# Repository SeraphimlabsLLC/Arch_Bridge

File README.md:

# Arch_Bridge

DCC-EX to Loconet accessory bus interface with throttle and booster driving. 

Additional 2A booster channel for future use

 Bidirectional transmission of turnout commands from Loconet to DCC-EX
 One way Throttle transmission, Loconet to DCC-EX

 Fastclock supplied to DCC-EX, still WIP getting it on Loconet

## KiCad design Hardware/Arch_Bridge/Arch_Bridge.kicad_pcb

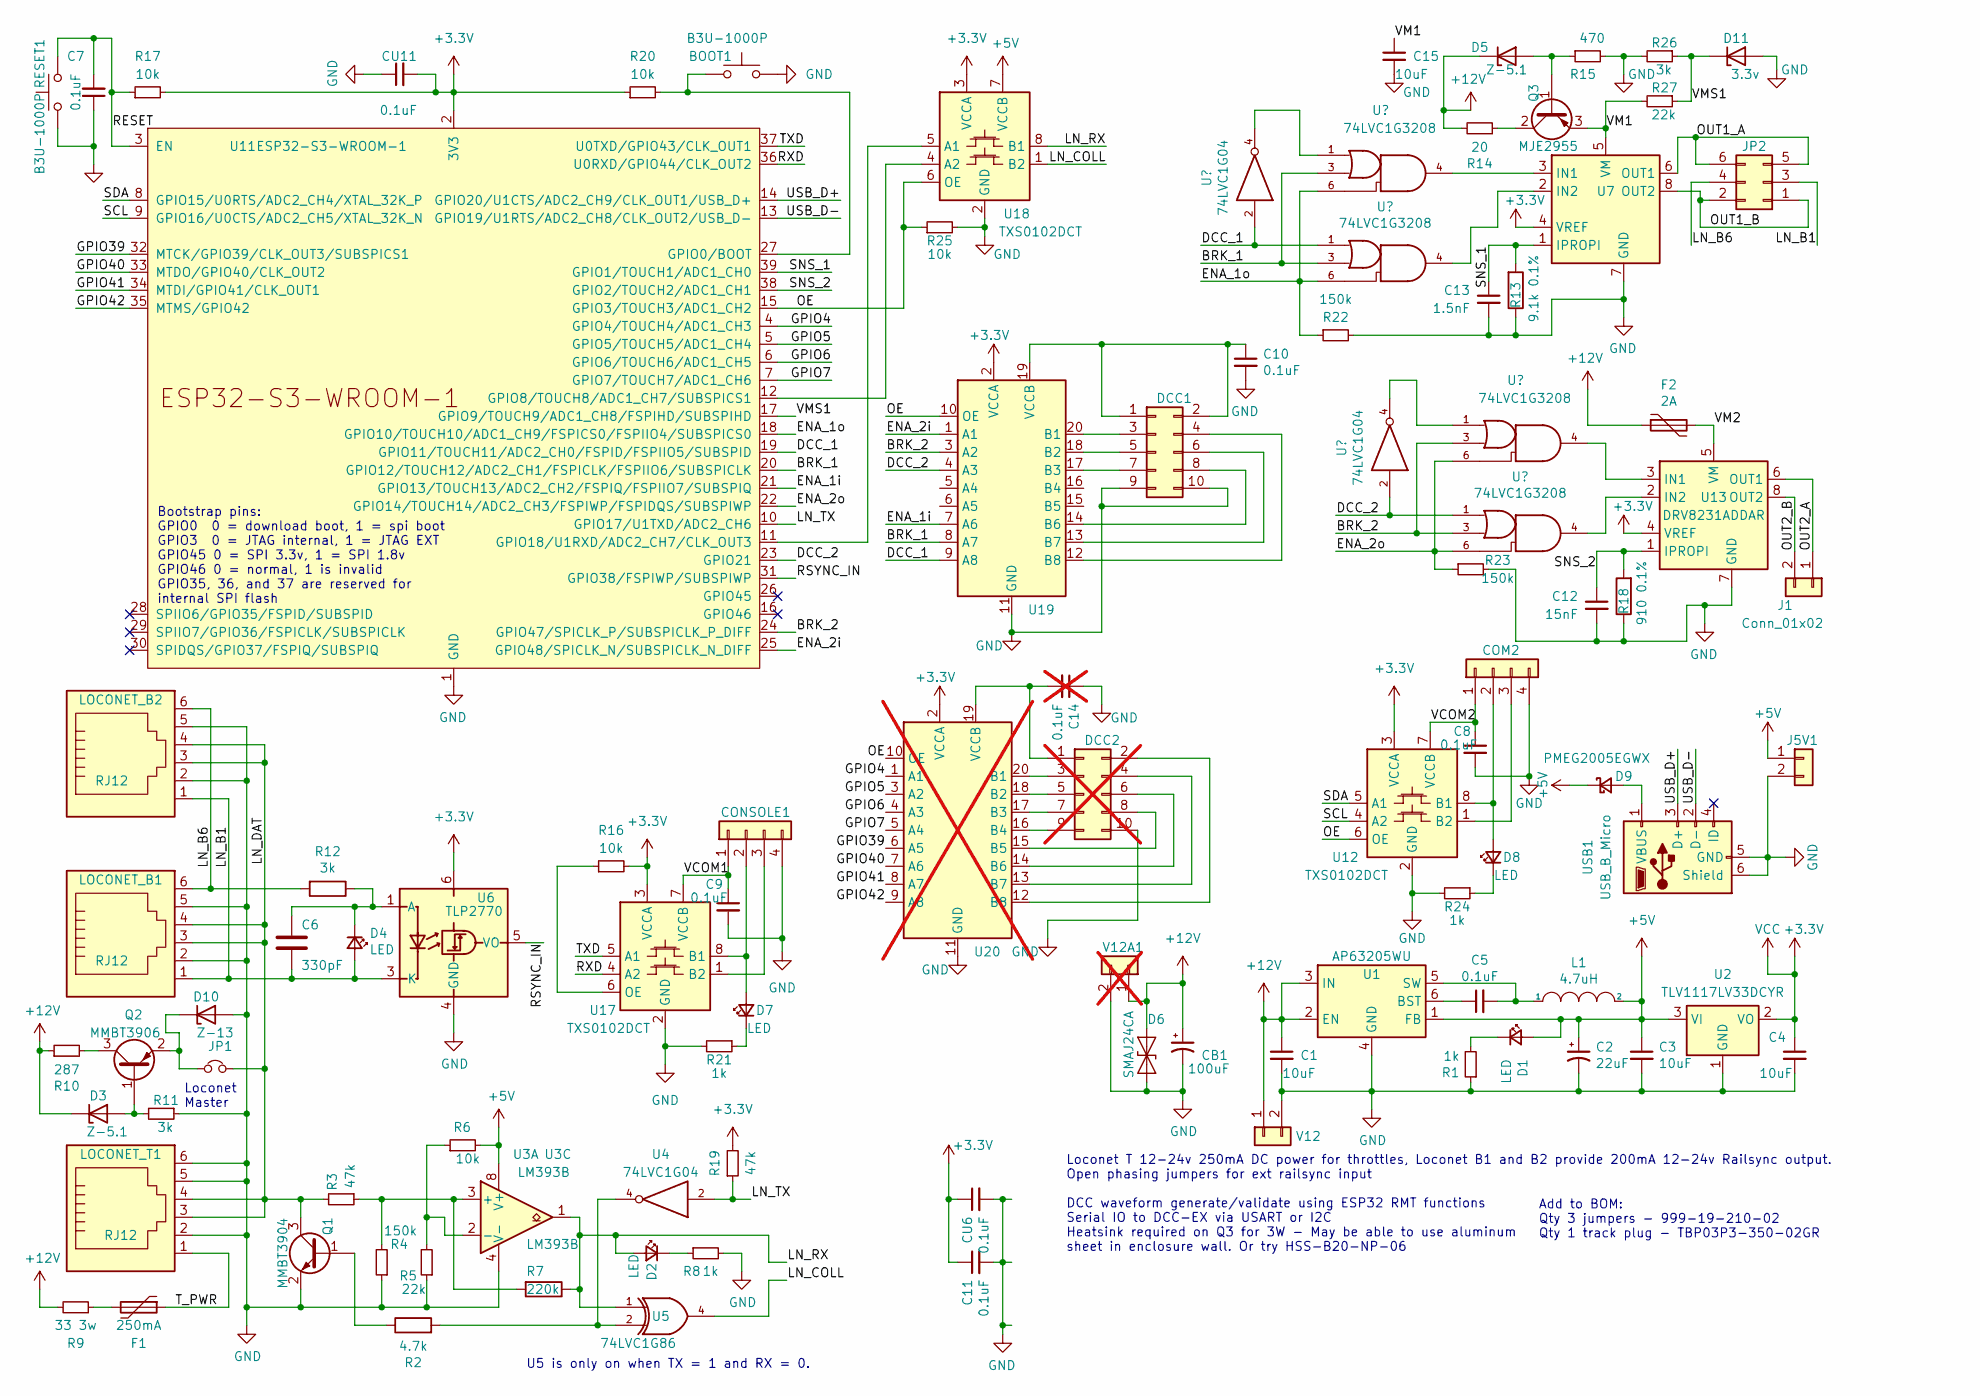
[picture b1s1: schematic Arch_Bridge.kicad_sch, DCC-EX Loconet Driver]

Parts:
BOOT1: B3U-1000P; SW_SPST_B3U-1000P-B; LCSC SKU C231329
C1, C3, C4, C15: 10uF; C_1210_3225Metric; LCSC SKU C380537
C2: 22uF; CP_Elec_5x5.3; LCSC SKU C2164091
C5, C7, C8, C9, C10, C11: 0.1uF; C_1206_3216Metric; LCSC SKU C600013
C6: 330pF; C_1206_3216Metric; LCSC SKU C2223641
C12: 15nF; C_1206_3216Metric_Pad1.33x1.80mm_HandSolder; LCSC SKU C2174116
C13: 1.5nF; C_1206_3216Metric_Pad1.33x1.80mm_HandSolder; LCSC SKU C2230319
C14: 0.1uF; C_1206_3216Metric; LCSC SKU C600013; not fitted
CB1: 100uF; CP_Elec_8x10; LCSC SKU C696384
COM2: Conn_01x04; PinSocket_1x04_P2.54mm_Vertical; LCSC SKU C3323964
CONSOLE1: Conn_01x04; PinSocket_1x04_P2.54mm_Vertical; LCSC SKU C3323964
CU6, CU11: 0.1uF; C_1206_3216Metric; LCSC SKU C600013
D1, D2, D4, D7, D8: LED; LED_1206_3216Metric
D3, D5: Z-5.1; D_MiniMELF; LCSC SKU C550442
D6: SMAJ24CA; D_SMA; LCSC SKU C148223
D9: PMEG2005EGWX; D_SOD-123; LCSC SKU C552812
D10: Z-13; D_MiniMELF; LCSC SKU C550391
D11: 3.3v; D_MiniMELF; LCSC SKU C550442
DCC1: Conn_02x05_Odd_Even; PinSocket_2x05_P2.54mm_Vertical; LCSC SKU C6235491
DCC2: Conn_02x05_Odd_Even; PinSocket_2x05_P2.54mm_Vertical; LCSC SKU C6235491; not fitted
F1: 250mA; Fuse_1206_3216Metric; LCSC SKU C2442492
F2: 2A; Fuse_Bourns_MF-RHT200; LCSC SKU C2153889
J1: Conn_01x02; PhoenixContact_MC_1,5_2-G-3.5_1x02_P3.50mm_Horizontal; LCSC SKU C880572
J5V1: Conn_01x02; PinSocket_1x02_P2.54mm_Vertical; LCSC SKU C3323491
JP1: Jumper_NC_Small; PinHeader_1x02_P2.54mm_Vertical; LCSC SKU C5172712
JP2: Conn_02x03_Odd_Even; PinHeader_2x03_P2.54mm_Vertical; LCSC SKU C6360273
L1: 4.7uH; L_Wurth_WE-LQSH-4020; LCSC SKU C167828
LOCONET_B1, LOCONET_B2: RJ12; RJ12_Amphenol_54601; LCSC SKU C4355015
LOCONET_T1: RJ12; RJ12_Amphenol_54601; LCSC SKU C4355015
Q1: MMBT3904; SOT-23; LCSC SKU C77991
Q2: MMBT3906; SOT-23; LCSC SKU C77990
Q3: MJE2955; TO-220-3_Vertical; LCSC SKU C184196
R1, R8, R21, R24: 1k; R_1206_3216Metric; LCSC SKU C131398
R2: 4.7k; R_1206_3216Metric; LCSC SKU C3975500
R3, R19: 47k; R_1206_3216Metric; LCSC SKU C137270
R4, R22, R23: 150k; R_1206_3216Metric; LCSC SKU C114931
R5, R27: 22k; R_1206_3216Metric; LCSC SKU C114942
R6, R16, R17, R20, R25: 10k; R_1206_3216Metric; LCSC SKU C4303232
R7: 220k; R_1206_3216Metric; LCSC SKU C130275
R9: 33 3w; R_Axial_DIN0516_L15.5mm_D5.0mm_P5.08mm_Vertical; LCSC SKU C1761032
R10: 287; R_1206_3216Metric; LCSC SKU C488764
R11, R12, R26: 3k; R_1206_3216Metric; LCSC SKU C132648
R13: 9.1k 0.1%; R_1206_3216Metric; LCSC SKU C706423
R14: 20; R_2512_6332Metric; LCSC SKU C309605
R15: 470; R_2512_6332Metric; LCSC SKU C872782
R18: 910 0.1%; R_1206_3216Metric; LCSC SKU C870936
RESET1: B3U-1000P; SW_SPST_B3U-1000P-B; LCSC SKU C231329
U1: AP63205WU; TSOT-23-6; LCSC SKU C2071056
U2: TLV1117LV33DCYR; SOT-223-3_TabPin2; LCSC SKU C91728
U3: LM393B; SOIC-8_3.9x4.9mm_P1.27mm; LCSC SKU C2865059
U4, U10, U16: 74LVC1G04; SOT-23-5_HandSoldering; LCSC SKU C7827
U5: 74LVC1G86; SOT-23-5_HandSoldering; LCSC SKU C402161
U6: TLP2770; SO-6L_10x3.84mm_P1.27mm; LCSC SKU C150160
U7, U13: DRV8231ADDAR; Texas_HTSOP-8-1EP_3.9x4.9mm_P1.27mm_EP2.95x4.9mm_Mask2.4x3.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
U8, U9, U14, U15: 74LVC1G3208; SOT-23-6_Handsoldering; LCSC SKU C2682152
U11: ESP32-S3-WROOM-1; ESP32-S3-WROOM-1U; LCSC SKU C2980298
U12, U17, U18: TXS0102DCT; SSOP-8_2.95x2.8mm_P0.65mm; LCSC SKU C2677354
U19: TXB0108PWR; TSSOP-20_4.4x6.5mm_P0.65mm; LCSC SKU C53406
U20: TXB0108PWR; TSSOP-20_4.4x6.5mm_P0.65mm; LCSC SKU C53406; not fitted
USB1: USB_B_Micro; USB_Micro-B_Molex-105017-0001; LCSC SKU C136000
V12: Conn_01x02; PhoenixContact_MSTBA_2,5_2-G_1x02_P5.00mm_Horizontal
V12A1: Conn_01x02; Screw_Terminal_2pin_Multicomp; not fitted

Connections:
+3.3V: C4.1, C11.1, CU6.1, CU11.2, R16.2, R17.2, R19.2, R20.1, U2.2 (VO), U6.6, U7.4 (VREF), U8.5 (VCC), U9.5 (VCC), U10.5 (VCC), U11.2 (3V3), U12.3 (VCCA), U13.4 (VREF), U14.5 (VCC), U15.5 (VCC), U16.5 (VCC), U17.3 (VCCA), U18.3 (VCCA), U19.2 (VCCA), U20.2 (VCCA)
+5V: C2.1, C3.1, D1.2 (A), D9.1 (K), J5V1.1, L1.2, R6.2, U1.1 (FB), U2.3 (VI), U3.8 (V+), U4.5 (+5V), U5.5 (+5V), U18.7 (VCCB)
+12V: C1.1, CB1.1, D3.1 (K), D5.1 (K), D6.1 (A1), F2.1, R9.2, R10.1, R14.2, U1.2 (EN), U1.3 (IN), V12.1, V12A1.1
/BRK_1: U8.3, U9.3, U11.20 (GPIO12/TOUCH12/ADC2_CH1/FSPICLK/FSPIIO6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), U19.8 (A7)
/BRK_2: U11.24 (GPIO47/SPICLK_P/SUBSPICLK_P_DIFF), U14.3, U15.3, U19.3 (A2)
/DCC_1: U9.1, U10.2, U11.19 (GPIO11/TOUCH11/ADC2_CH0/FSPID/FSPIIO5/S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), U19.9 (A8)
/DCC_2: U11.23 (GPIO21), U15.1, U16.2, U19.4 (A3)
/ENA_1i: U11.21 (GPIO13/TOUCH13/ADC2_CH2/FSPIQ/FSPIIO7/S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), U19.7 (A6)
/ENA_1o: R22.1, U8.6, U9.6, U11.18 (GPIO10/TOUCH10/ADC1_CH9/FSPICS0/FSPIIO4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)
/ENA_2i: U11.25 (GPIO48/SPICLK_N/SUBSPICLK_N_DIFF), U19.1 (A1)
/ENA_2o: R23.1, U11.22 (GPIO14/TOUCH14/ADC2_CH3/FSPIWP/FSPIDQS/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), U14.6, U15.6
/GPIO4: U11.4 (GPIO4/TOUCH4/ADC1_CH3), U20.1 (A1)
/GPIO5: U11.5 (GPIO5/TOUCH5/ADC1_CH4), U20.3 (A2)
/GPIO6: U11.6 (GPIO6/TOUCH6/ADC1_CH5), U20.4 (A3)
/GPIO7: U11.7 (GPIO7/TOUCH7/ADC1_CH6), U20.5 (A4)
/GPIO39: U11.32 (MTCK/GPIO39/CLK_OUT3/SUBSPICS1), U20.6 (A5)
/GPIO40: U11.33 (MTDO/GPIO40/CLK_OUT2), U20.7 (A6)
/GPIO41: U11.34 (MTDI/GPIO41/CLK_OUT1), U20.8 (A7)
/GPIO42: U11.35 (MTMS/GPIO42), U20.9 (A8)
/LN_B1: C6.2, D4.2 (A), JP2.3, LOCONET_B1.1, LOCONET_B2.1, U6.3 (K)
/LN_B6: JP2.4, LOCONET_B1.6, LOCONET_B2.6, R12.2
/LN_COLL: U5.4, U18.1 (B2)
/LN_DAT: JP1.2, LOCONET_B1.3, LOCONET_B1.4, LOCONET_B2.3, LOCONET_B2.4, LOCONET_T1.3, LOCONET_T1.4, Q1.3 (C), R3.2
/LN_RX: D2.2 (A), R7.1, U3.1, U5.1, U18.8 (B1)
/LN_TX: R19.1, U4.2, U11.10 (GPIO17/U1TXD/ADC2_CH6)
/OE: R25.1, U11.15 (GPIO3/TOUCH3/ADC1_CH2), U12.6 (OE), U18.6 (OE), U19.10 (OE), U20.10 (OE)
/OUT1_A: JP2.5, JP2.6, U7.6 (OUT1)
/OUT1_B: JP2.1, JP2.2, U7.8 (OUT2)
/OUT2_A: J1.1, U13.6 (OUT1)
/OUT2_B: J1.2, U13.8 (OUT2)
/RESET: C7.2, R17.1, RESET1.2, U11.3 (EN)
/RSYNC_IN: U6.5 (VO), U11.31 (GPIO38/FSPIWP/SUBSPIWP)
/RXD: U11.36 (U0RXD/GPIO44/CLK_OUT2), U17.4 (A2)
/SCL: U11.9 (GPIO16/U0CTS/ADC2_CH5/XTAL_32K_N), U12.4 (A2)
/SDA: U11.8 (GPIO15/U0RTS/ADC2_CH4/XTAL_32K_P), U12.5 (A1)
/SNS_1: C13.1, R13.2, U7.1 (IPROPI), U11.39 (GPIO1/TOUCH1/ADC1_CH0)
/SNS_2: C12.1, R18.2, U11.38 (GPIO2/TOUCH2/ADC1_CH1), U13.1 (IPROPI)
/TXD: U11.37 (U0TXD/GPIO43/CLK_OUT1), U17.5 (A1)
/T_PWR: F1.1, LOCONET_T1.1
/USB_D+: U11.14 (GPIO20/U1CTS/ADC2_CH9/CLK_OUT1/USB_D+), USB1.3 (D+)
/USB_D-: U11.13 (GPIO19/U1RTS/ADC2_CH8/CLK_OUT2/USB_D-), USB1.2 (D-)
/VCOM1: C9.1, CONSOLE1.1, U17.7 (VCCB)
/VCOM2: C8.1, COM2.1, U12.7 (VCCB)
/VM1: C15.1, Q3.3 (E), R27.2, U7.5 (VM)
/VM2: F2.2, U13.5 (VM)
/VMS1: D11.1 (K), R26.1, R27.1, U11.17 (GPIO9/TOUCH9/ADC1_CH8/FSPIHD/SUBSPIHD)
GND: BOOT1.1, C1.2, C2.2, C3.2, C4.2, C7.1, C8.2, C9.2, C10.2, C11.2, C12.2, C13.2, C14.1, C15.2, CB1.2, COM2.4, CONSOLE1.4, CU6.2, CU11.1, D6.2 (A2), D10.2 (A), D11.2 (A), DCC1.9, DCC1.10, DCC2.10, J5V1.2, LOCONET_B1.2, LOCONET_B1.5, LOCONET_B2.2, LOCONET_B2.5, LOCONET_T1.2, LOCONET_T1.5, LOCONET_T1.6, Q1.2 (E), R1.1, R4.1, R5.1, R8.2, R11.1, R13.1, R15.2, R18.1, R21.2, R22.2, R23.2, R24.2, R25.2, R26.2, RESET1.1, U1.4 (GND), U2.1 (GND), U3.4 (V-), U4.3 (GND), U5.3 (GND), U6.4 (GND), U7.7 (GND), U7.9 (GND), U8.2 (GND), U9.2 (GND), U10.3 (GND), U11.1 (GND), U11.40 (GND), U11.41 (GND), U12.2 (GND), U13.7 (GND), U13.9 (GND), U14.2 (GND), U15.2 (GND), U16.3 (GND), U17.2 (GND), U18.2 (GND), U19.11 (GND), U20.11 (GND), USB1.5 (GND), USB1.6 (Shield), V12.2, V12A1.2; also elsewhere on the board
unnamed: COM2.2, D8.2 (A), U12.8 (B1)
unnamed: COM2.3, U12.1 (B2)
unnamed: CONSOLE1.2, D7.2 (A), U17.8 (B1)
unnamed: CONSOLE1.3, U17.1 (B2)
unnamed: D1.1 (K), R1.2
unnamed: D2.1 (K), R8.1
unnamed: D3.2 (A), Q2.1 (B), R11.2
unnamed: C6.1, D4.1 (K), R12.1, U6.1 (A)
unnamed: D5.2 (A), Q3.1 (B), R15.1
unnamed: D7.1 (K), R21.1
unnamed: D8.1 (K), R24.1
unnamed: D9.2 (A), USB1.1 (VBUS)
unnamed: D10.1 (K), JP1.1, Q2.2 (E)
unnamed: C10.1, DCC1.1, DCC1.2, U19.19 (VCCB)
unnamed: DCC1.3, U19.20 (B1)
unnamed: DCC1.4, U19.12 (B8)
unnamed: DCC1.5, U19.18 (B2)
unnamed: DCC1.6, U19.13 (B7)
unnamed: DCC1.7, U19.17 (B3)
unnamed: DCC1.8, U19.14 (B6)
unnamed: C14.2, DCC2.1, U20.19 (VCCB)
unnamed: DCC2.2, U20.12 (B8)
unnamed: DCC2.3, U20.20 (B1)
unnamed: DCC2.4, U20.13 (B7)
unnamed: DCC2.5, U20.18 (B2)
unnamed: DCC2.6, U20.14 (B6)
unnamed: DCC2.7, U20.17 (B3)
unnamed: DCC2.8, U20.15 (B5)
unnamed: DCC2.9, U20.16 (B4)
unnamed: F1.2, R9.1
unnamed: Q1.1 (B), R2.1
unnamed: Q2.3 (C), R10.2
unnamed: Q3.2 (C), R14.1
unnamed: R2.2, U4.4, U5.2
unnamed: C5.1, U1.6 (BST)
unnamed: C5.2, L1.1, U1.5 (SW)
unnamed: R3.1, R4.2, R7.2, U3.3 (+)
unnamed: R5.2, R6.1, U3.2 (-)
unnamed: U7.3 (IN1), U8.4
unnamed: U7.2 (IN2), U9.4
unnamed: U8.1, U10.4
unnamed: BOOT1.2, R20.2, U11.27 (GPIO0/BOOT)
unnamed: U11.12 (GPIO8/TOUCH8/ADC1_CH7/SUBSPICS1), U18.4 (A2)
unnamed: U11.11 (GPIO18/U1RXD/ADC2_CH7/CLK_OUT3), U18.5 (A1)
unnamed: U13.3 (IN1), U14.4
unnamed: U13.2 (IN2), U15.4
unnamed: U14.1, U16.4
unnamed: R16.1, U17.6 (OE)

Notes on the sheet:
Loconet T 12-24v 250mA DC power for throttles, Loconet B1 and B2 provide 200mA 12-24v Railsync output. Open phasing jumpers for ext railsync input DCC waveform generate/validate using ESP32 RMT functions Serial IO to DCC-EX via USART or I2C Heatsink required on Q3 for 3W - May be able to use alumin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
U5 is only on when TX = 1 and RX = 0.
Loconet Master
Add to BOM: Qty 3 jumpers - 999-19-210-02 Qty 1 track plug - TBP03P3-350-02GR
Bootstrap pins: GPIO0 0 = download boot, 1 = spi boot GPIO3 0 = JTAG internal, 1 = JTAG EXT GPIO45 0 = SPI 3.3v, 1 = SPI 1.8v GPIO46 0 = normal, 1 is invalid GPIO35, 36, and 37 are reserved for internal SPI flash

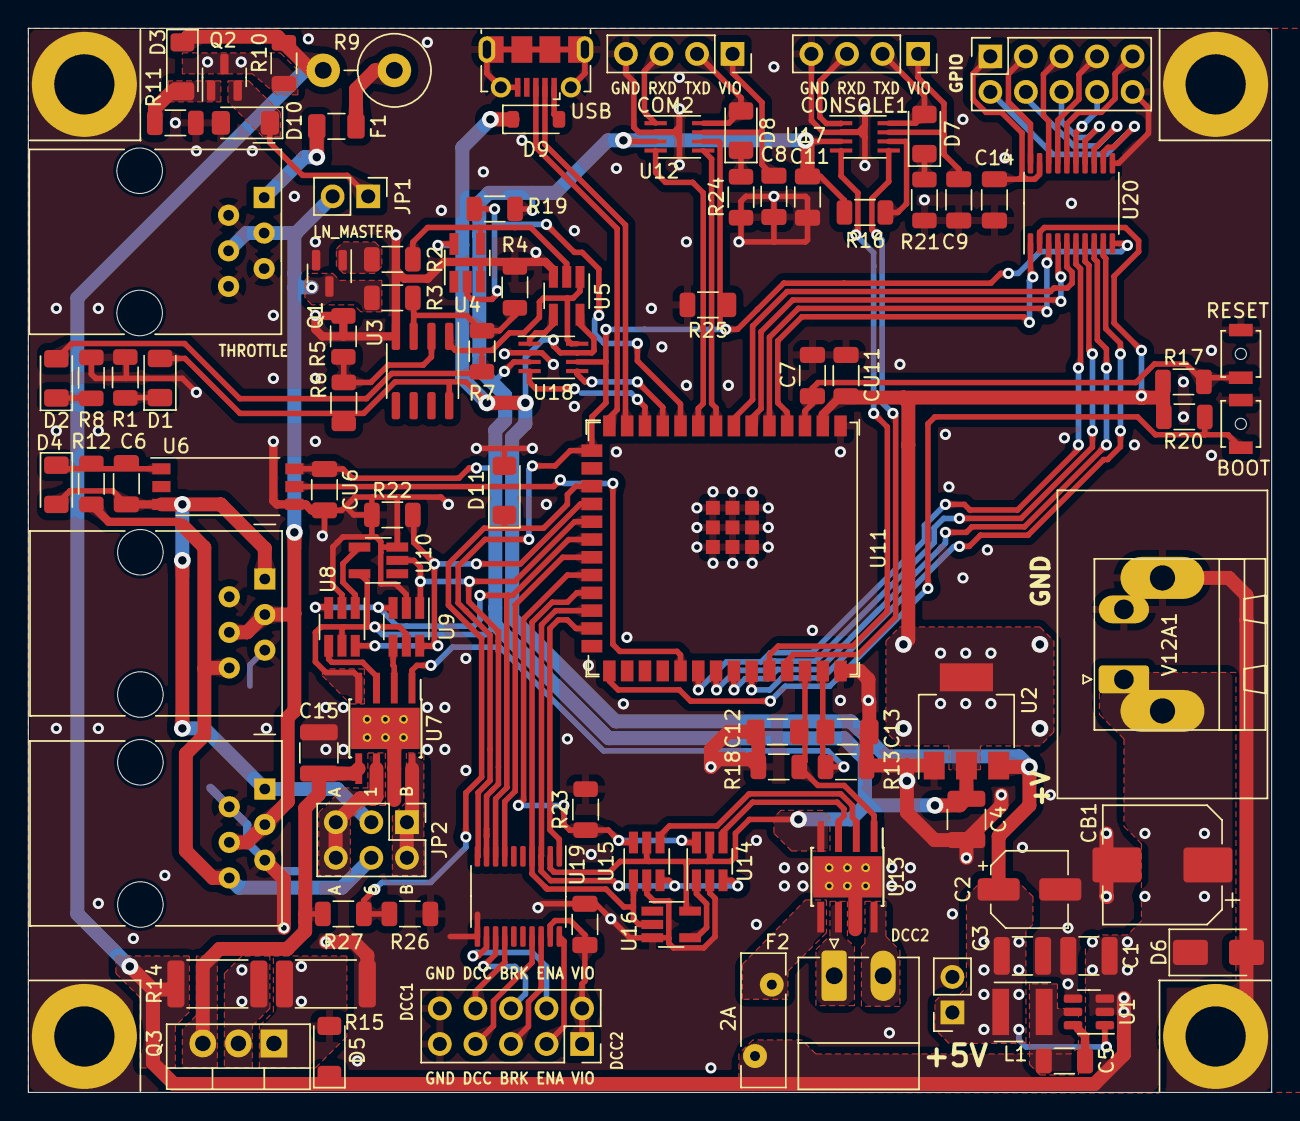
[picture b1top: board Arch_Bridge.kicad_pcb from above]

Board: 2 copper layers, 88.8 x 76.0 mm, 101 parts (0 on the bottom side), 95 nets.

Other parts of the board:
H1, H2, H4: MountingHole_Pad; MountingHole_4.3mm_M4_DIN965_Pad

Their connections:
GND: H1.1, H2.1, H4.1; also elsewhere on the board

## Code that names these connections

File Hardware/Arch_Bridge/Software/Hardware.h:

//ADC Settings:
#DEFINE ADC_DMAX 4095 //4095 in single shot, 8191 in continuous
#DEFINE ADC_VMAX 3.1 //Max readable voltage is actually 3.1v using mode ADC_ATTEN_DB_11  

//TTY settings:
/* Pin Map
TXD = GPIO43(U0TXD)
RXD = GPIO44(U0RXD)
*/
#DEFINE TTY_TX_BUFF = 4096
#DEFINE TTY_RX_BUFF = 4096

//I2C settings: 
/* Pin Map
SDA = GPIO15
SCL = GPIO16
*/
#DEFINE I2C_TX_BUFF = 4096
#DEFINE I2C_RX_BUFF = 4096

//Loconet settings:
/* Pin Map
LN_TX = GPIO17(U1RXD)
LN_RX = GPIO18 (U1RXD)
LN_COLL = GPIO0
*/
#DEFINE LN_TX_BUFF = 4096
#DEFINE LN_RX_BUFF = 4096

//Railsync input settings:
/* Pin Map
RSYNC_IN = GPIO9
*/

//Railsync output settings:
/*  Pin Map
ENA_10 = GPIO10
DCC_1 = GPIO11
BRK_1 = GPIO12
ENA_1i = GPIO13
SNS1 = GPIO1(ADC1_CH0)
*/
#DEFINE OUT1_MAX_A 3610 //ADC_DMAX / ADC_VMAX * SENSE_V for 200mA + 0.1%

//Track output settings:
/* Pin Map
ENA_20 = GPIO14
DCC_2 = GPIO21
BRK_2 = GPIO47
ENA_2i = GPIO48
SNS2 = GPIO2(ADC1_CH1)
*/
#DEFINE OUT2_MAX_A 3610 //ADC_DMAX / ADC_VMAX * SENSE_V for 2A + 0.1%

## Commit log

2023-07-27 Adding hardware brief in README.md
2023-07-27 Folder structure for hardware/software and KiCad solution
2023-07-30 Completed BOM, PCB layout cleanup, starting software.
2023-07-30 Add PDF schematic
2023-07-30 Configured initial .gitignore
2023-08-20 Revised L1 for possible 2A output, cleaner fill zones, fabrication outputs
2023-08-21 BOM Cleanup, substitute 3.3v LDO for easier to get part.
2023-08-27 Update .gitignore
    Ignore KiCad backups
2023-09-28 First build using this hardware for software development.
2023-09-28 Added .gitignore
2023-09-29 ESP_Uart class added, has problems still and Arduino Serial library acting as a placeholder.
2023-09-29 Prep to move uart code and loconet code into separate files
2023-09-29 Rough split of uart code into its own files
2023-10-03 Power modes partially implemented. Railsync output H bridge handled a test waveform correctly.
2023-10-09 ADC testing, progress reading from Loconet.
2023-10-12 Progress on Loconet parser
2023-10-16 Loconet RX/TX still not working.
2023-10-16 Loconet uart is able to send data, but still needs transmission rules
2023-10-16 Loconet UART working in both RX and TX. Can finally write the parsers.
2023-10-21 Progress on DCC-EX parser
2023-10-21 Fixed R11 value, 33k => 3k so that Q2 sources correctly. Tested at 14.5mA on a 12v supply.
2023-10-22 Adjusted R15 value and ADC code to make railsync current source work correctly. 0-208mA availabe.
2023-11-04 Preliminary Loconet CD, refining LN receive processing. Will need to rewrite TX data handling.
2023-11-05 Moved track handling loop into its own function in ESP_Tracks.cpp. RMT RX startup implemented, still needs read functions.
2023-11-08 New classes for Loconet Packets and Loconet Slots. Significant layout of logic flow in preparation for a rewrite of Loconet transmission.
2023-11-10 TX Packet mostly works, RX scan not working properly.
2023-11-13 Loconet rx and tx packet handling mostly working, has some crashes. Begin framing RMT
2023-11-14 DCC bits to packets, temporarially using Arduino RMT library
2023-11-16 Success at last getting config.example.h to work, __has_include wasn't working. Cleaned up main, remnants of ring buffers in uart, and laid out the dccex parser
2023-11-16 Testing tty input
2023-11-17 Console parser input possible. Loconet still erratic/crashing.
2023-11-20 Fixed Uart read issue in ESP32_Uart.cpp. Attempt at Fastclock handler in ESP32_timer so that it is accessible outside loconet too.
2023-11-26 TX Loopback still has problems
2023-11-28 Schematic rev 06 with PCB updates. Needs BOM and Fabs reprocessed.
2023-12-04 Fixed Loconet packet processing. Fault was in packet size handling. TX confirmation by loopback works.
2023-12-05 Loconet slot manager successfully accepting throttle inputs. Still needs bridging to DCC-EX.
2023-12-05 Remove debug files
2023-12-05 Cleaning up slot handling, connecting output to DCCEX
2023-12-08 Fastclock and Turnouts shared between DCC-EX and Loconet
2023-12-09 Throttle commands from Loconet to DCC-EX working. Still need opposite direction.
2023-12-09 Changed calculation of frac_mins in Loconet fastclock handling. Will still drift relative to a DCS100.
2023-12-10 Cleaned up uart code, removed unnecessary tx buffer
2023-12-12 Attempt to send DCC-EX throttle changes back to Loconet throttles
2023-12-17 Changed CB1 to through hole for field installaion, no longer in BOM or populated by default.
2023-12-17 Added tags for JLCPCB Fabricaton
2023-12-22 More predictable Loconet TX_Q speeds. RX_Q similarly optimized, but continues to show high mS spike. Crashes on collision detect.
2023-12-22 Added Loconet opcode 0xB5, stat1 write
2023-12-22 Split DCC bit processing and parsing into dcc_read.cpp and dcc_read.h. Added temporary pcint based detector since RMT continues to not work.
2023-12-23 DCC signal detection operational. Packets are not actually parsed, but are assembled and checksum calculated. Touchd up track mode, power, and check enable.
2023-12-24 Reworked TrackChannel::StateChange to use - values for overload, 0 for off, +1 for on_fwd, and +2 for on_rev
2023-12-24 Changed ADC calculations to be x1000 instead of x1000000 so the values fit int32_t instead of int64_t.
2023-12-25 Testing aux 2A output
2023-12-29 Fixed DCC-EX track manager syntax to correctly work with text mode labels.
2023-12-31 Schematic rev 0.8, PCB update adding current sense filter caps, fixing pull-up on Loconet TX, and slight reposition of U17
2023-12-31 Schematic rev 0.8, fixed teardrops
2024-01-10 Changed aux track output to use 5.0mm pitch matching EX-8874 track plugs
2024-01-10 Forgot to add pad teardrops again.
2024-01-14 Revised VIN to 5v power supply for better performance and less PCB space
2024-01-14 Relocated aux output for better cooling
2024-01-16 Fixed bug in TX_Loopback() that was causing crash. TX cooldown now uses a PCINT + timestamp for more reliable detection of network state.
2024-01-16 Diag: Calculate time between tx_send() and 1st edge. Measuring around 320uS, needs to be <2uS
2024-01-16 Fixed disconnect/reconnect detection
2024-01-19 Test point
2024-01-30 BOM fix, replace NCP1117 with TLV1117
2024-03-21 R15 could overheat, changed R14 and R15 to 2512 package SMDs for 1w thermal and simplified assembly. PCB rev 11. Also debugging of Loconet TX delay and throttle/turnout commands
2024-03-22 Split transmit LN speed and LN dir into separate functions
2024-03-22 Fixed turnout address calculation, fixed disconnect detection
2024-04-03 Checkpoint
2024-04-16 Revised PCB to fix thermal problems, improve usage of board space. DCC inputs, serial ports, and GPIO all have independent IOREF connections.
2024-04-22 Board revision progress
2024-04-22 Fixed bug turning off enable out
2024-04-23 Added Railsync voltage monitoring circuit, stabilizer cap. Updated BOM with new parts.
2024-04-23 Schematic update to match PCB r.14
2024-04-23 Replaced TXS0108E with TXB0108 to make use of auto-off feature when ioref is not powered
2024-04-24 ESP32-dccex rx_scanrejects packets above 255 chars length
2024-06-10 Fixed BOM error for JP2, should have been 2x3 pin header not socket.
2024-06-11 Conversion to ESP32 Core 3.0 (IDF 5.1). ADC does not work, incomplete restructuring to continuous mode.
2024-06-11 IDF5.1: ADC not working, continuous ADC config possible.
2024-06-14 ADC inoperative, continuous read ISR incomplete
2024-06-14 Slot 127 data populated, currently fixed values only.
2024-06-28 slot 127 changes
2024-06-28 ADC Continuous config present, no callback
2024-06-29 ADC Continuous enabled, no ISR or output yet
2024-06-30 ADC Continuous enabled, fixed <c> display, no ISR or data yet
2024-06-30 Fixed ADC setup structure to more reliably pass necessary data. Still no usable output
2024-07-18 ADC runs but doesn't read properly.
2024-07-21 Loconet host mode enum for restricting commands. Layout power command processing from Loconet to DCC-EX and back partially working.
2024-07-21 Loconet power on/off repeats to DCCEX. Known bug where you have to hit off twice for it to actually shut off.
2024-07-21 Loconet <=> DCCEX power and estop working
2024-08-28 Loconet transmit break using micros() timer \n
2024-10-13 Checkpoint before making changes to get hardware timers
2024-10-16 Loconet BREAK changed to gptimer
2024-10-16 Added volatile flag byte for transmit active and received break so the pin change ISR can notify the loop
2024-11-08 Bugfix: Console commands are no longer parsed twice. Restructured dccex parser data input slightly. \n
2024-12-05 ADC as a separate task, but using analogRead again.
2024-12-05 Overload handling and power state/mode mutex implemntation \n
2024-12-05 Loconet BREAK handling found defective.
2024-12-20 Notes on ADC Continuous to try repairing it with
2024-12-31 ADC Continuous partially working
2024-12-31 ADC Continuous Read operational at last.
2024-12-31 ADC Continuous Read operational at last. Increased ADC sample rate to 30khz
2025-01-25 Converted to Arduino ESP core 3.1, aka IDF 5.3
2025-03-18 Further implementation of accessory state table
2025-03-22 Corrected Loconet timer control issue
